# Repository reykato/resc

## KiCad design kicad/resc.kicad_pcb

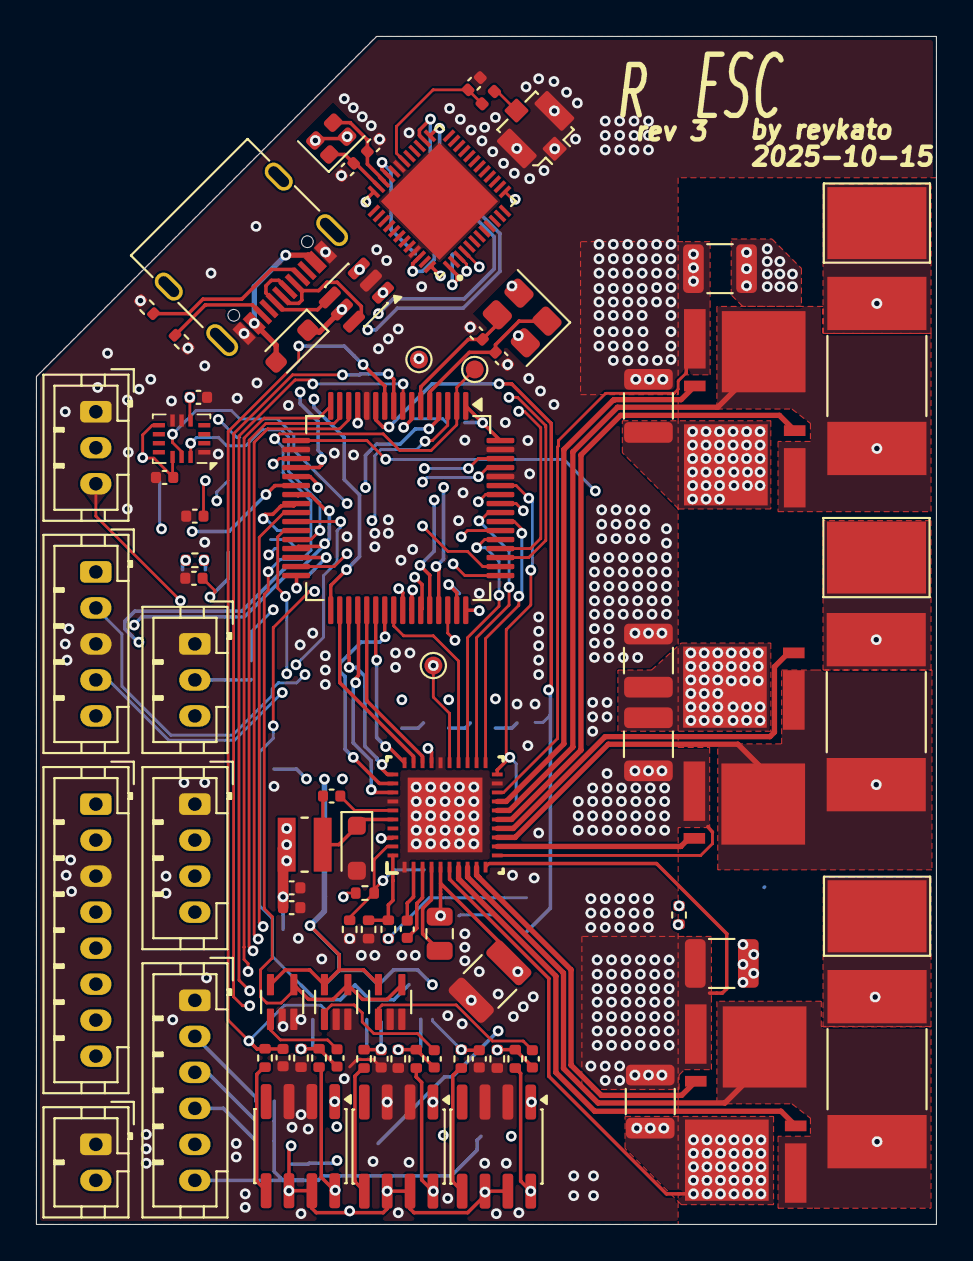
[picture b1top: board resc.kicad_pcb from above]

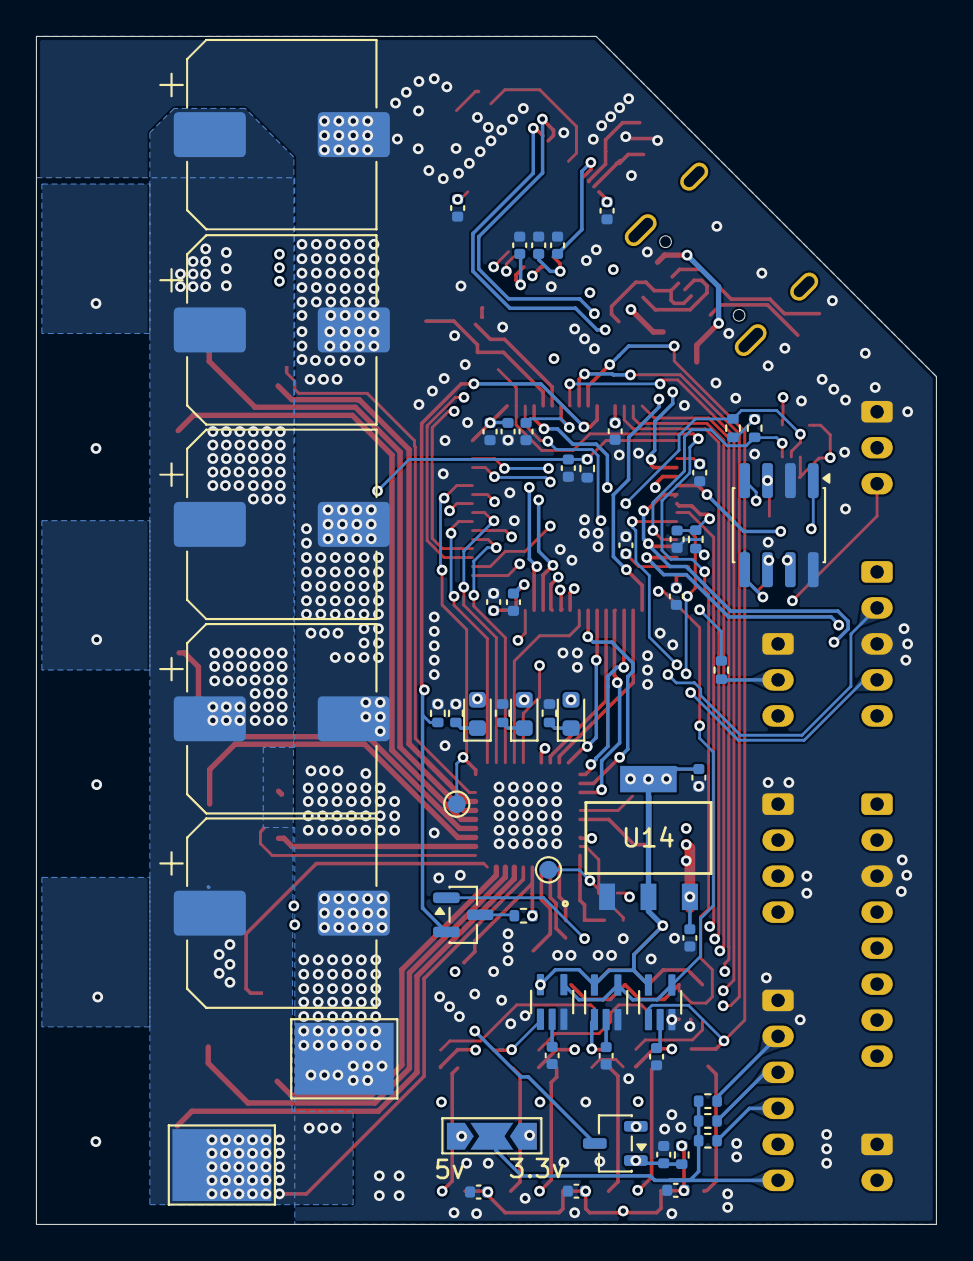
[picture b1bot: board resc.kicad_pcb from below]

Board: 4 copper layers, 50.0 x 66.0 mm, 148 parts (59 on the bottom side), 109 nets.

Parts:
C1, C3, C11, C20, C22, C30, C35, C58: 100nF; C_0402_1005Metric
C2, C5, C6, C7, C8, C9, C10, C14, C15, C16, C17, C36, C37, C44, C45, C46, C55, C56: 2.2uF; C_0402_1005Metric
C12, C13: 15pF; C_0402_1005Metric
C18: 47nF; C_0402_1005Metric
C19: 1uF 63V; C_0805_2012Metric
C21, C38, C39, C40, C41, C42, C43: 4.7uF 100V; C_1210_3225Metric
C23, C24: 2.2uF 10V; C_0402_1005Metric
C25, C26, C27, C28, C53: 220uF 63V; CP_Elec_10x10
C47, C48, C49: 1nF; C_0402_1005Metric
C50, C51, C52: 15nF; C_0402_1005Metric
C59, C62: 8pF; C_0402_1005Metric
C60, C61: 4.7uF; C_0402_1005Metric
C63: 100pF; C_0402_1005Metric
C64: 1uF; C_0402_1005Metric
C65: 0.8pF; C_0402_1005Metric
D1: GREEN; LED_0603_1608Metric
D2: BLUE; LED_0603_1608Metric
D3: RED; LED_0603_1608Metric
D8, D10: D_Schottky; D_SOD-323_HandSoldering
J1: CAN; JST_PH_B4B-PH-K_1x04_P2.00mm_Vertical
J2: HALL; JST_PH_B6B-PH-K_1x06_P2.00mm_Vertical
J3: COMM; JST_PH_B8B-PH-K_1x08_P2.00mm_Vertical
J4: POWER BTN; JST_PH_B2B-PH-K_1x02_P2.00mm_Vertical
J5: SERVO; JST_PH_B3B-PH-K_1x03_P2.00mm_Vertical
J6: SWD; JST_PH_B5B-PH-K_1x05_P2.00mm_Vertical
J7: LED1; JST_PH_B3B-PH-K_1x03_P2.00mm_Vertical
J9: USB_C_Receptacle_USB2.0_14P; USB_C_Receptacle_G-Switch_GT-USB-7010ASV
J10: Conn_Coaxial; U.FL_Molex_MCRF_73412-0110_Vertical
L1: 22uH; IND_VLS3010CX-220M-1
L2: 3.9nH; L_0402_1005Metric
NT1, NT2, NT3, NT4: NetTie_2; NetTie-2_SMD_Pad0.2mm
Q1, Q2, Q3, Q4, Q5, Q6: IRF7749L1; TRANS_BSC014N04LSIATMA1_Custom_NoSilkscreen
Q7: DMN62D0UW-7; SOT-23
Q8: DMG3415U; SOT-23-3
R1, R9, R12, R22: 10k; R_0402_1005Metric
R2, R3, R4, R20, R26, R30, R44: 2.2k; R_0402_1005Metric
R5, R7, R13, R14, R18: 220R; R_0402_1005Metric
R6, R8, R11, R40, R41, R42: 1k; R_0402_1005Metric
R10: 100k; R_0402_1005Metric
R19, R23, R29: 39k 60V; R_0402_1005Metric
R21: 56k; R_0402_1005Metric
R34, R35, R36: 0.0005R; RESC10052X105N
R43: 39k; R_0402_1005Metric
R45, R46: 5.1k; R_0402_1005Metric
SW1: SENSOR_VOLTAGE; SolderJumper-3_P2.0mm_Open_TrianglePad1.0x1.5mm_NumberLabels
TH1: NTC 10k; R_0402_1005Metric
TP1: nSHDN; TestPoint_Pad_D1.0mm
TP2: SENS_FILT; TestPoint_Pad_D1.0mm
TP3: SUPPLY; TestPoint_Pad_5.5x4.0mm
TP4: PH_A; TestPoint_Pad_5.5x4.0mm
TP5: PH_B; TestPoint_Pad_5.5x4.0mm
TP6: PH_C; TestPoint_Pad_5.5x4.0mm
TP7: GND; TestPoint_Pad_5.5x4.0mm
TP8: CONN_SW; TestPoint_Pad_D1.0mm
TP10: nFAULT; TestPoint_Pad_D1.0mm
TP11: EN_DRV; TestPoint_Pad_D1.0mm
U1: STM32F405RGTx; LQFP-64_10x10mm_P0.5mm
U2: TJA1051T-3; SOIC-8_3.9x4.9mm_P1.27mm
U3, U5, U6, U11, U12, U13: SN74LVC1G66DCKR; SOT65P210X110-5N_Custom
U4: DRV8320RSRHAR; RHA0040B_NV
U7: BMI160; Bosch_LGA-14_3x2.5mm_P0.5mm
U8, U9, U10: AD8418; SOIC-8_3.9x4.9mm_P1.27mm
U14: TC2117-3.3VDBTR; SOT-223_3MC_MCH_Custom
U15: USBLC6-2SC6; SOT-23-6
U16: NRF52832-QFAA-R; QFN40P600X600X90-49N
Y1: 8MHz; Crystal_SMD_3225-4Pin_3.2x2.5mm
Y2: 32MHz; Crystal_SMD_2016-4Pin_2.0x1.6mm

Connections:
+5V: C16.1, C17.1, C23.1, C24.1, C55.1, D10.1 (K), J1.4, J3.1, J5.2, J7.3, L1.2, Q7.1 (G), R21.2, SW1.1 (A), U2.3 (VCC), U2.5 (VIO), U14.3 (VI), U15.5 (VBUS)
/BLE/BLE_RX: U1.51 (PC10), U16.4 (P0_02/AIN0)
/BLE/BLE_TX: U1.52 (PC11), U16.3 (P0_01/XL2)
/BLE/SWDCLK: U1.20 (PA4), U16.25 (SWDCLK)
/BLE/SWDIO: U1.33 (PB12), U16.26 (SWDIO)
/CAN/CANH: J1.2, R18.1, U2.7 (CANH)
/CAN/CANL: J1.3, R18.2, U2.6 (CANL)
/CAN/RX: U1.61 (PB8), U2.4 (RXD)
/CAN/TX: U1.62 (PB9), U2.1 (TXD)
/CONN_SW: C3.1, J3.8, J4.2, Q8.G, R12.2, TP8.1, U1.4 (PC15)
/Gate Driver/CS: U1.40 (PC9), U4.24 (CS)
/Gate Driver/EN_DRV: TP11.1, U1.57 (PB5), U4.25 (ENABLE)
/Gate Driver/GH_A: Q1.G, U4.7 (GHA)
/Gate Driver/GH_B: Q2.G, U4.14 (GHB)
/Gate Driver/GH_C: Q3.G, U4.15 (GHC)
/Gate Driver/GL_A: Q4.G, U4.9 (GLA)
/Gate Driver/GL_B: Q5.G, U4.12 (GLB)
/Gate Driver/GL_C: Q6.G, U4.17 (GLC)
/Gate Driver/INH_A: U1.37 (PC6), U4.28 (INHA)
/Gate Driver/INH_B: U1.38 (PC7), U4.30 (INHB)
/Gate Driver/INH_C: U1.39 (PC8), U4.32 (INHC)
/Gate Driver/INL_A: U1.34 (PB13), U4.29 (INLA)
/Gate Driver/INL_B: U1.35 (PB14), U4.31 (INLB)
/Gate Driver/INL_C: U1.36 (PB15), U4.33 (INLC)
/Gate Driver/SCK: U1.53 (PC12), U4.23 (SCLK)
/Gate Driver/SDI: U1.56 (PB4), U4.22 (SDI)
/Gate Driver/SDO: U1.55 (PB3), U4.21 (SDO)
/Gate Driver/SENS_FILTERED: TP2.1, U1.2 (PC13), U3.4 (C), U5.4 (C), U6.4 (C)
/Gate Driver/SH_A: Q1.S, Q4.D, R19.2, R34.1, U4.8 (SHA), U8.8 (IN+)
/Gate Driver/SH_B: Q2.S, Q5.D, R23.2, R35.1, U4.13 (SHB), U9.8 (IN+)
/Gate Driver/SH_C: Q3.S, Q6.D, R29.2, R36.1, U4.16 (SHC), U10.8 (IN+)
/Gate Driver/SL_A: NT1.1, U4.10 (SLA)
/Gate Driver/SL_B: NT2.1, U4.11 (SLB)
/Gate Driver/SL_C: NT3.1, U4.18 (SLC)
/Gate Driver/SUPPLY: C19.1, C21.1, C25.1, C26.1, C27.1, C28.1, C38.1, C39.1, C40.1, C41.1, C42.1, C43.1, C53.1, NT4.1, Q1.D, Q2.D, Q3.D, R43.1, TP3.1, U4.5 (VM), U4.38 (VIN)
/Gate Driver/VOLTAGE_A: C22.1, R19.1, R20.1, U1.14 (PA0)
/Gate Driver/VOLTAGE_B: C30.1, R23.1, R26.1, U1.15 (PA1)
/Gate Driver/VOLTAGE_C: C35.1, R29.1, R30.1, U1.16 (PA2)
/Gate Driver/nFAULT: TP10.1, U1.59 (PB7), U4.20 (nFAULT)
/IMU/SCL: R8.2, U1.50 (PA15), U7.13 (SCx)
/IMU/SDA: R11.2, U1.28 (PB2), U7.14 (SDx)
/MCU/AN_IN: Q7.2 (S), R44.1, U1.11 (PC3)
/MCU/CURRENT_1: C47.1, R40.1, U1.8 (PC0), U11.1 (A)
/MCU/CURRENT_2: C48.1, R41.1, U1.9 (PC1), U12.1 (A)
/MCU/CURRENT_3: C49.1, R42.1, U1.10 (PC2), U13.1 (A)
/MCU/CURR_FILT_ON: U1.54 (PD2), U11.4 (C), U12.4 (C), U13.4 (C)
/MCU/HALL_1: J2.4, R2.1, U1.41 (PA8)
/MCU/HALL_2: J2.3, R3.1, U1.42 (PA9)
/MCU/HALL_3: J2.2, R4.1, U1.43 (PA10)
/MCU/LED1: R14.1, U1.3 (PC14)
/MCU/LED_GREEN: D1.2 (A), U1.26 (PB0)
/MCU/LED_RED: D3.2 (A), U1.27 (PB1)
/MCU/MISO_ADC_EXT2: J3.7, U1.22 (PA6)
/MCU/NRST: C11.1, J6.1, U1.7 (NRST)
/MCU/RX_SDA_NSS: J3.5, U1.30 (PB11)
/MCU/SCK_ADC_EXT: J3.4, U1.21 (PA5)
/MCU/SERVO: J5.3, U1.58 (PB6)
/MCU/SWCLK: J6.4, U1.49 (PA14)
/MCU/SWDIO: J6.2, U1.46 (PA13)
/MCU/TEMP_MOTOR: C1.1, J2.5, R1.2, U1.24 (PC4)
/MCU/TX_SCL_MOSI: J3.6, U1.23 (PA7), U1.29 (PB10)
/MCU/USB_DM: U1.44 (PA11), U15.1 (I/O1)
/MCU/USB_DP: U1.45 (PA12), U15.3 (I/O2)
/MOSFETs/C_A: R40.2, U8.5 (OUT)
/MOSFETs/C_B: R41.2, U9.5 (OUT)
/MOSFETs/C_C: R42.2, U10.5 (OUT)
/MOSFETs/PH_A: R34.2, TP4.1, U8.1 (IN-)
/MOSFETs/PH_B: R35.2, TP5.1, U9.1 (IN-)
/MOSFETs/PH_C: R36.2, TP6.1, U10.1 (IN-)
/POWER: R13.2, U1.25 (PC5)
/TEMP: C2.1, R9.1, TH1.2, U1.17 (PA3)
/nSHDN: Q8.D, R10.2, R13.1, TP1.1, U4.39 (nSHDN)
GND: C1.2, C2.2, C3.2, C5.2, C6.2, C7.2, C8.2, C9.2, C10.2, C11.2, C12.2, C13.2, C14.2, C15.2, C16.2, C17.2, C21.2, C23.2, C24.2, C25.2, C26.2, C27.2, C28.2, C36.2, C37.2, C38.2, C39.2, C40.2, C41.2, C42.2, C43.2, C44.2, C45.2, C46.2, C47.2, C48.2, C49.2, C50.2, C51.2, C52.2, C53.2, C55.2, C56.2, C58.1, C59.1, C60.1, C61.1, C62.1, C63.1, C64.1, C65.2, D8.2 (A), J1.1, J2.1, J3.3, J4.1, J5.1, J6.3, J7.1, J9.A1 (GND), J9.A12 (GND), J9.B1 (GND), J9.B12 (GND), J10.2 (Ext), NT1.2, NT2.2, NT3.2, Q4.S, Q5.S, Q6.S, R5.1, R6.2, R7.1, R9.2, R10.1, R20.2, R22.1, R26.2, R30.2, R44.2, R45.2, R46.2, TP7.1, U1.12 (VSSA), U1.18 (VSS), U1.60 (BOOT0), U1.63 (VSS), U2.2 (GND), U2.8 (S), U3.2 (B), U3.3 (GND), U4.1 (PGND), U4.19 (GND), U4.26 (AGND), U4.34 (BGND), U4.41 (PAD), U5.2 (B), U5.3 (GND), U6.2 (B), U6.3 (GND), U7.1 (SDO), U7.6 (GNDIO), U7.7 (GND), U8.2 (GND), U8.3 (REF2), U9.2 (GND), U9.3 (REF2), U10.2 (GND), U10.3 (REF2), U11.3 (GND), U12.3 (GND), U13.3 (GND), U14.1 (GND), U15.2 (GND), U16.31 (VSS), U16.45 (VSS__1), U16.49 (EXP), Y1.2, Y1.4, Y2.2, Y2.4
unnamed: D1.1 (K), R5.2
unnamed: D2.1 (K), R6.1
unnamed: D3.1 (K), R7.2
unnamed: C20.1, D8.1 (K), L1.1, U4.36 (SW)
unnamed: D10.2 (A), J9.A4 (VBUS), J9.A9 (VBUS), J9.B4 (VBUS), J9.B9 (VBUS)
unnamed: J2.6, R2.2, R3.2, R4.2, SW1.2 (B)
unnamed: J7.2, R14.2
unnamed: J9.A5 (CC1), R45.1
unnamed: J9.B5 (CC2), R46.1
unnamed: J9.A6 (D+), J9.B6 (D+), U15.4 (I/O2)
unnamed: J9.A7 (D-), J9.B7 (D-), U15.6 (I/O1)
unnamed: J10.1 (In), L2.2
unnamed: Q7.3 (D), R43.2
unnamed: C12.1, U1.5 (PH0), Y1.1
unnamed: C13.1, U1.6 (PH1), Y1.3
unnamed: C14.1, U1.31 (VCAP_1)
unnamed: C15.1, U1.47 (VCAP_2)
unnamed: C22.2, U3.1 (A)
unnamed: C20.2, U4.35 (CB)
unnamed: C18.1, U4.3 (CPH)
unnamed: C18.2, U4.2 (CPL)
unnamed: R21.1, R22.2, U4.40 (FB)
unnamed: C19.2, U4.4 (VCP)
unnamed: NT4.2, U4.6 (VDRAIN)
unnamed: C30.2, U5.1 (A)
unnamed: C35.2, U6.1 (A)
unnamed: C50.1, U11.2 (B)
unnamed: C51.1, U12.2 (B)
unnamed: C52.1, U13.2 (B)
unnamed: C65.1, L2.1, U16.30 (ANT)
unnamed: C61.2, U16.1 (DEC1)
unnamed: C63.2, U16.33 (DEC3)
unnamed: C64.2, U16.46 (DEC4)
unnamed: C59.2, U16.34 (XC1), Y2.3
unnamed: C62.2, U16.35 (XC2), Y2.1
VDD: C5.1, C6.1, C7.1, C8.1, C9.1, C10.1, C36.1, C37.1, C44.1, C45.1, C46.1, C56.1, C58.2, C60.2, D2.2 (A), J3.2, J6.5, Q8.S, R1.1, R8.1, R11.1, R12.1, SW1.3 (C), TH1.1, U1.1 (VBAT), U1.13 (VDDA), U1.19 (VDD), U1.32 (VDD), U1.48 (VDD), U1.64 (VDD), U3.5 (VCC), U4.27 (DVDD), U5.5 (VCC), U6.5 (VCC), U7.5 (VDDIO), U7.8 (VDD), U7.12 (CSB), U8.6 (VS), U8.7 (REF1), U9.6 (VS), U9.7 (REF1), U10.6 (VS), U10.7 (REF1), U11.5 (VCC), U12.5 (VCC), U13.5 (VCC), U14.2 (VO), U16.13 (VDD), U16.36 (VDD__1), U16.48 (VDD__2)

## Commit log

2025-08-10 this build works
2025-08-10 added rev0 of hardware design
2025-08-10 checking shunt footprints
2025-08-10 forgot to close kicad
2025-08-10 working on fet fp
2025-08-11 routing gate driver
2025-08-11 gate driver routed to mosfets, working on misc stm32 related components
2025-08-11 done? without test points
2025-08-29 revision 1, drv won't power on right?
2025-09-02 finalizing schematic for gate driver
2025-09-05 revision 2 is complete, sent to manufacturer
2025-09-25 add kicad changes (there probably aren't any actual changes)
2025-09-25 revert to v6.05
2025-10-08 working version! mostly!
2025-10-13 gate driver mostly schematic'd and pcb started
2025-10-13 missed saving pcb
2025-11-10 rev3 ordered
